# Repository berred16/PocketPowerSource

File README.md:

# PocketPowerSource
Handheld power source for educational purpose

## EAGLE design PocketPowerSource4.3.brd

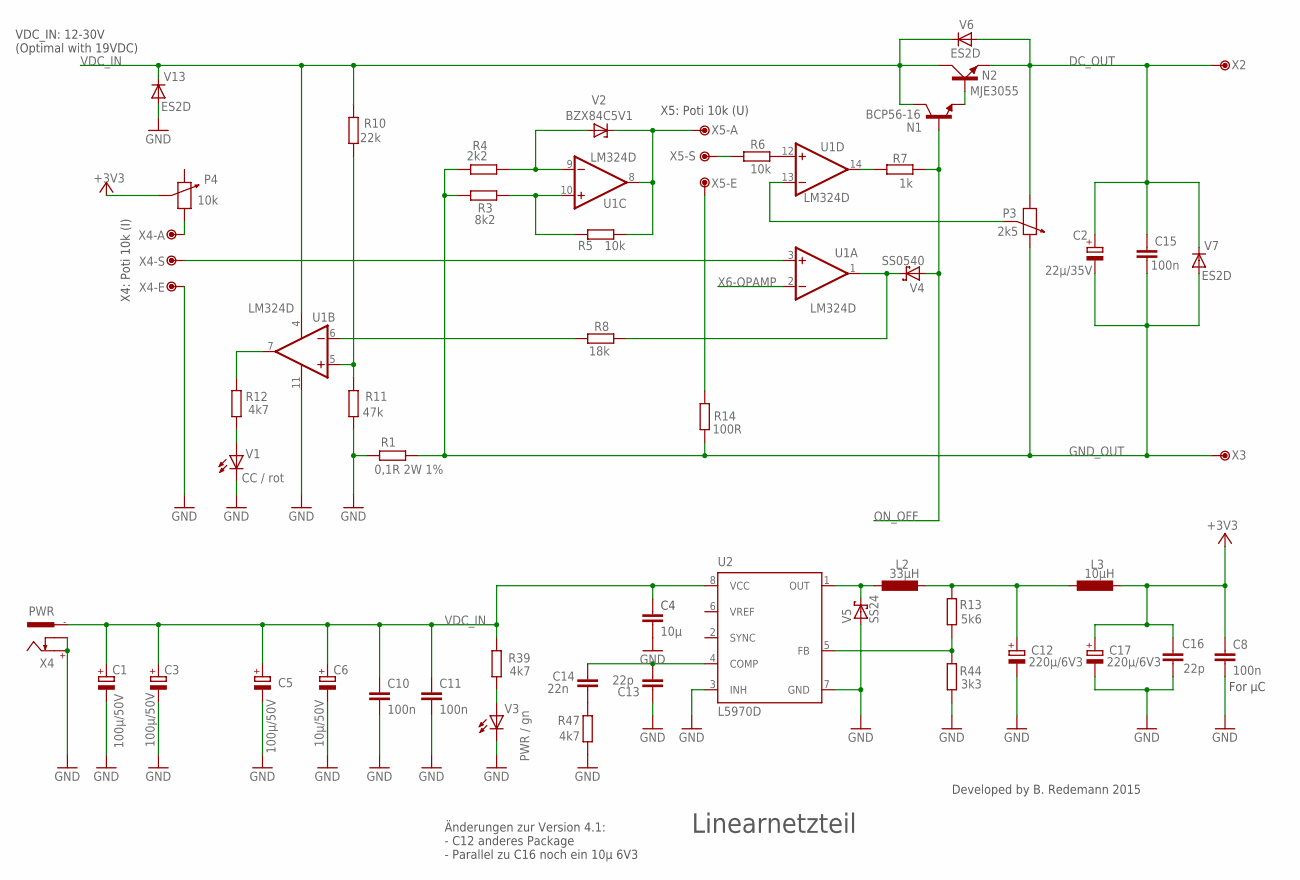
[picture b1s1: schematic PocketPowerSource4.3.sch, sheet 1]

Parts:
C1, C3, C5: 100µ/50V; PANASONIC_F
C2: 22µ/35V; PANASONIC_C
C4: 10µ; C1210
C6: 10µ/50V; PANASONIC_D
C8, C10, C11, C15: 100n; C0603K
C12, C17: 220µ/6V3; PANASONIC_D
C13, C16: 22p; C0805
C14: 22n; C1206
L2: 33µH; POWER-CHOKE_WE-TPC
L3: 10µH; L4540
N1: BCP56-16; PG-SOT-223
N2: MJE3055; TO220AV
P3: 2k5; PT6
P4: 10k; PT6
R1: 0,1R 2W 1%; R2512
R3: 8k2; R0603
R4: 2k2; R0805
R5, R6: 10k; R0603
R7: 1k; R0603
R8: 18k; R1206
R10: 22k; R0603
R11: 47k; R0603
R12, R39, R47: 4k7; R1206
R13: 5k6; R0603
R14: 100R; R0603
R44: 3k3; R0603
U1: LM324D; SO14
U2: L5970D; SO08
V1: CC / rot; LED3MM
V2: BZX84C5V1; TO236
V3: PWR / gn; LED3MM
V4: SS0540; SOD123
V5: SS24; SMB
V6, V7, V13: ES2D; SMB
X2: DC_OUT; P1-13
X3: GND_OUT; P1-13
X4: PWR; 737992-5
X4-A: P_I-A; P1-13
X4-E: P_I-E; P1-13
X4-S: P_I-W; P1-13
X5-A: P_U-A; P1-13
X5-E: P_U-E; P1-13
X5-S: P_U-S; P1-13

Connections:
+3V3: C8.1, C16.2, C17.+, L3.P$2 (2), P4.WIPER (1S); also elsewhere on the board
DC_OUT: C2.+, C15.1, N2.E, P3.RIGHT (1E), V6.A, V7.C, X2.TP; also elsewhere on the board
GND: C1.-, C3.-, C4.2, C5.-, C6.-, C8.2, C10.2, C11.2, C12.-, C13.1, C16.1, C17.-, R1.2, R11.1, R44.1, R47.1, U1.11 (V-), U2.3 (INH), U2.7 (GND), V1.K (C), V3.K (C), V5.A, V13.A, X4.+, X4.K, X4-E.TP; also elsewhere on the board
GND_OUT: C2.-, C15.2, P3.LEFT (1A), R1.1, R3.1, R4.1, R14.2, V7.A, X3.TP; also elsewhere on the board
unnamed: R8.1, U1.6 (-IN)
unnamed: R5.1, U1.8 (OUT), V2.C, X5-A.TP
unnamed: R12.1, U1.7 (OUT)
unnamed: P4.RIGHT (1E), X4-A.TP
unnamed: R12.2, V1.A
unnamed: R8.2, U1.1 (OUT), V4.C
unnamed: R3.2, R5.2, U1.10 (+IN)
unnamed: R4.2, U1.9 (-IN), V2.A
unnamed: N1.3 (E), N2.B
unnamed: R7.2, U1.14 (OUT)
unnamed: C13.2, C14.1, U2.4 (COMP)
unnamed: R10.1, R11.2, U1.5 (+IN)
unnamed: R6.2, U1.12 (+IN)
unnamed: P3.WIPER (1S), U1.13 (-IN)
unnamed: R6.1, X5-S.TP
unnamed: R14.1, X5-E.TP
unnamed: U1.3 (+IN), X4-S.TP
unnamed: C12.+, L2.2, L3.P$1 (1), R13.2
unnamed: R39.1, V3.A
unnamed: R13.1, R44.2, U2.5 (FB)
unnamed: C14.2, R47.2
unnamed: L2.1, U2.1 (OUT), V5.C
ON_OFF: N1.1 (B), R7.1, V4.A; also elsewhere on the board
VDC_IN: C1.+, C3.+, C4.1, C5.+, C6.+, C10.1, C11.1, N1.2 (C), N1.4 (C), N2.C, R10.2, R39.2, U1.4 (V+), U2.8 (VCC), V6.C, V13.C, X4.-1; also elsewhere on the board
X6-OPAMP: U1.2 (-IN); also elsewhere on the board

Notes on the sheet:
Linearnetzteil
VDC_IN: 12-30V (Optimal with 19VDC)
For µC
X4: Poti 10k (I)
X5: Poti 10k (U)
Developed by B. Redemann 2015
Änderungen zur Version 4.1: - C12 anderes Package - Parallel zu C16 noch ein 10µ 6V3

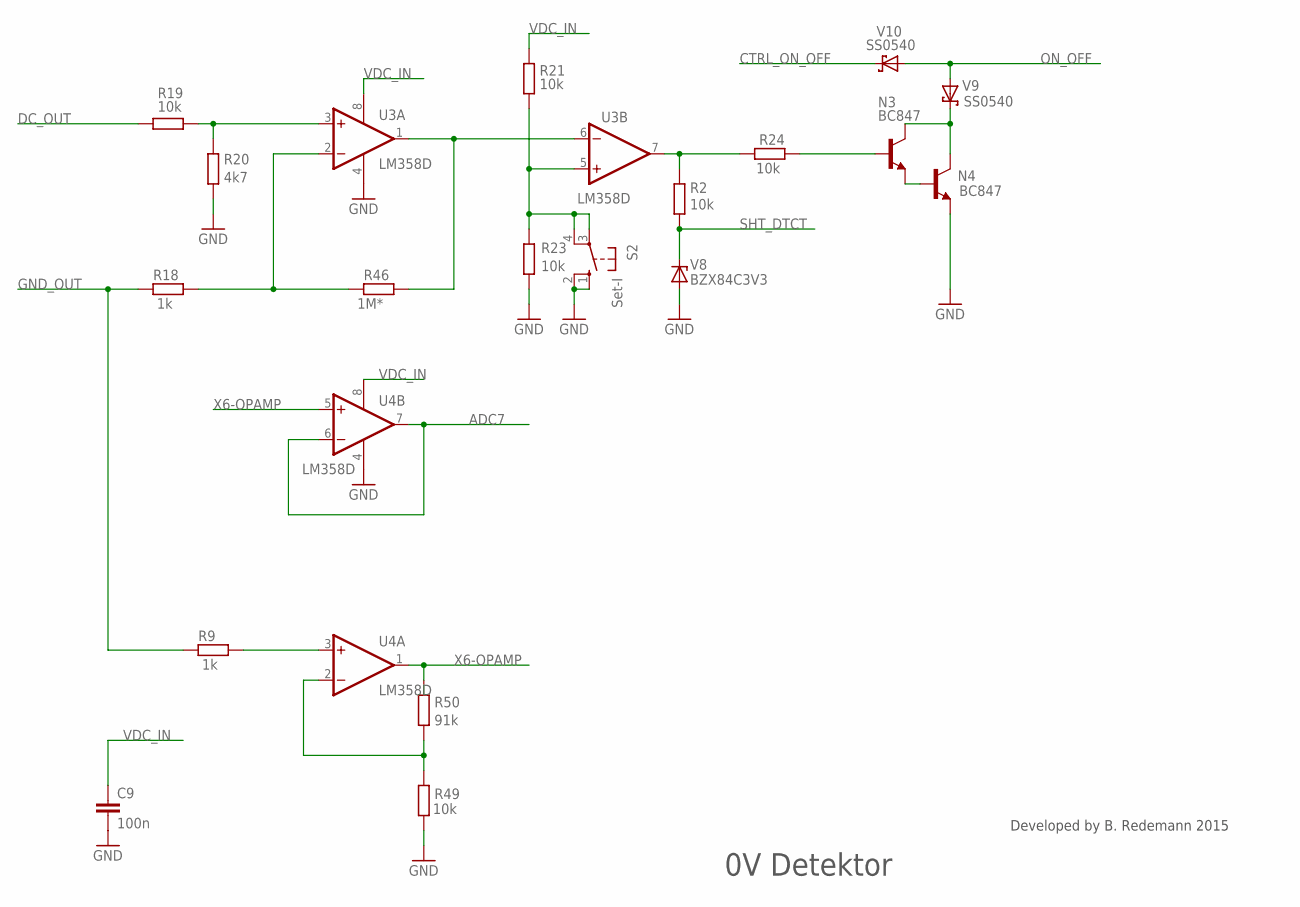
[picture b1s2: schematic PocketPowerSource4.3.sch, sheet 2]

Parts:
C9: 100n; C0603K
N3, N4: BC847; SOT23
R2, R19, R21, R23, R24, R49: 10k; R0603
R9, R18: 1k; R0603
R20: 4k7; R1206
R46: 1M*; R0603
R50: 91k; R0805
S2: Set-I; B3F-10XX
U3, U4: LM358D; SO08
V8: BZX84C3V3; TO236
V9, V10: SS0540; SOD123

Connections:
ADC7: U4.6 (-IN), U4.7 (OUT); also elsewhere on the board
CTRL_ON_OFF: V10.C; also elsewhere on the board
DC_OUT: R19.1; also elsewhere on the board
GND: C9.2, N4.2 (E), R20.1, R23.1, R49.1, S2.1 (S), S2.2 (S1), U3.4 (V-), U4.4 (V-), V8.A; also elsewhere on the board
GND_OUT: R9.1, R18.1; also elsewhere on the board
unnamed: R19.2, R20.2, U3.3 (+IN)
unnamed: R9.2, U4.3 (+IN)
unnamed: N3.1 (B), R24.2
unnamed: R2.2, R24.1, U3.7 (OUT)
unnamed: R18.2, R46.1, U3.2 (-IN)
unnamed: R46.2, U3.1 (OUT), U3.6 (-IN)
unnamed: R21.1, R23.2, S2.3, S2.4 (P1), U3.5 (+IN)
unnamed: R49.2, R50.1, U4.2 (-IN)
unnamed: N3.2 (E), N4.1 (B)
unnamed: N3.3 (C), N4.3 (C), V9.C
ON_OFF: V9.A, V10.A; also elsewhere on the board
SHT_DTCT: R2.1, V8.C; also elsewhere on the board
VDC_IN: C9.1, R21.2, U3.8 (V+), U4.8 (V+); also elsewhere on the board
X6-OPAMP: R50.2, U4.1 (OUT), U4.5 (+IN); also elsewhere on the board

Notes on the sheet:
0V Detektor
Developed by B. Redemann 2015

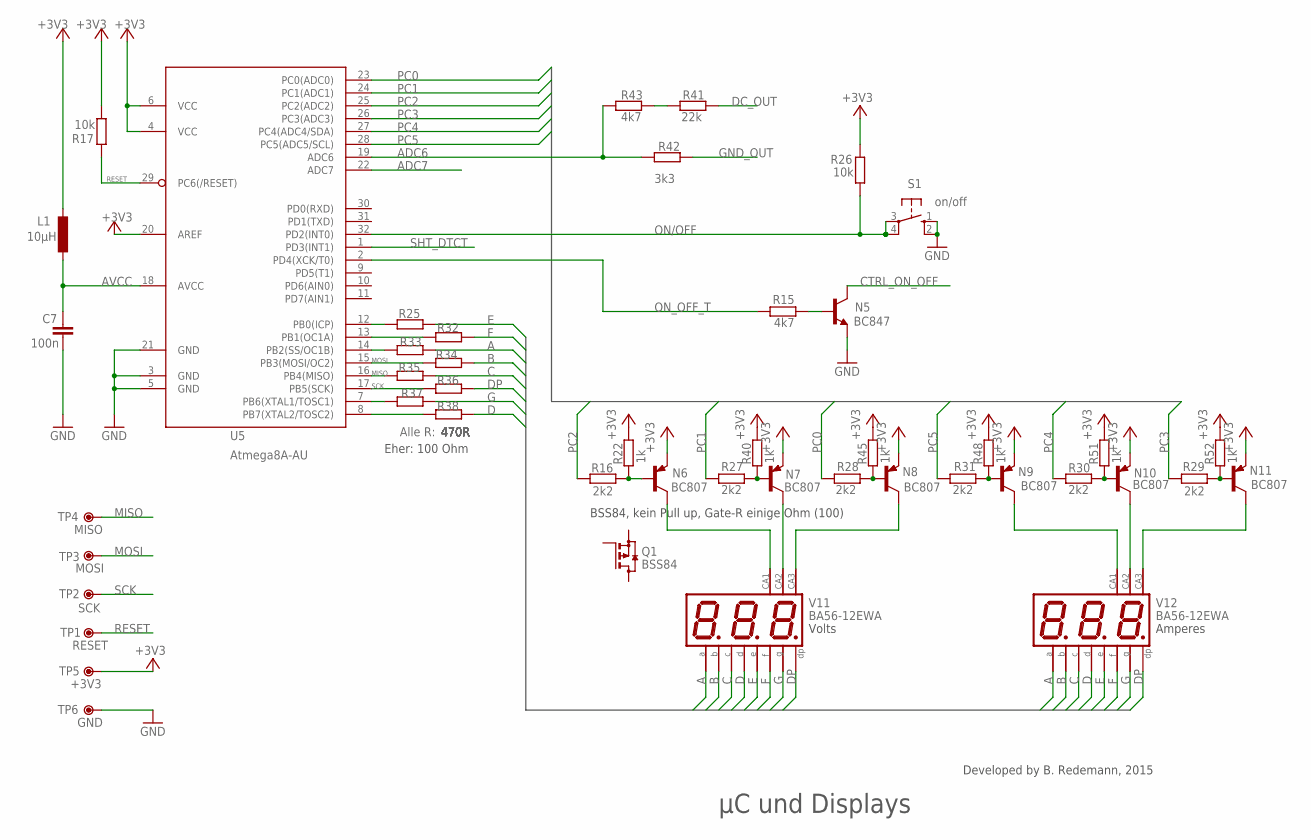
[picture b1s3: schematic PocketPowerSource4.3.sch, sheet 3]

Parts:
C7: 100n; C0603K
L1: 10µH; L2825P
N5: BC847; SOT23
N6, N7, N8, N9, N10, N11: BC807; SOT23-BEC
Q1: BSS84; SOT23
R15, R43: 4k7; R1206
R16, R27, R28, R29, R30, R31: 2k2; R1206
R17, R26: 10k; R0603
R22, R40, R45, R48, R51, R52: 1k; R0603
R25, R32, R33, R34, R35, R36, R37, R38: 470R; R0805
R41: 22k; R0603
R42: 3k3; R0603
S1: on/off; B3F-10XX
TP1: RESET; P1-13
TP2: SCK; P1-13
TP3: MOSI; P1-13
TP4: MISO; P1-13
TP5: +3V3; P1-13
TP6: GND; P1-13
U5: Atmega8A-AU; TQFP32-08
V11, V12: BA56-12EWA; BX56-12

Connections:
+3V3: L1.1, N6.E, N7.E, N8.E, N9.E, N10.E, N11.E, R17.1, R22.2, R26.2, R40.2, R45.2, R48.2, R51.2, R52.2, TP5.TP, U5.4 (VCC), U5.6 (VCC), U5.20 (AREF); also elsewhere on the board
A: R33.1, V11.11 (A), V12.11 (A)
ADC6: R42.1, R43.1, U5.19 (ADC6)
ADC7: U5.22 (ADC7); also elsewhere on the board
AVCC: C7.1, L1.2, U5.18 (AVCC)
B: R34.1, V11.7 (B), V12.7 (B)
C: R35.1, V11.4 (C), V12.4 (C)
CTRL_ON_OFF: N5.3 (C); also elsewhere on the board
D: R38.1, V11.2 (D), V12.2 (D)
DC_OUT: R41.2; also elsewhere on the board
DP: R36.1, V11.3 (DP), V12.3 (DP)
E: R25.1, V11.1 (E), V12.1 (E)
F: R32.1, V11.10 (F), V12.10 (F)
G: R37.1, V11.5 (G), V12.5 (G)
GND: C7.2, N5.2 (E), S1.1 (S), S1.2 (S1), TP6.TP, U5.3 (GND), U5.5 (GND), U5.21 (GND); also elsewhere on the board
GND_OUT: R42.2; also elsewhere on the board
MISO: R35.2, TP4.TP, U5.16 (PB4(MISO))
MOSI: R34.2, TP3.TP, U5.15 (PB3(MOSI/OC2))
unnamed: R41.1, R43.2
unnamed: N5.1 (B), R15.1
unnamed: N6.B, R16.2, R22.1
unnamed: R25.2, U5.12 (PB0(ICP))
unnamed: R32.2, U5.13 (PB1(OC1A))
unnamed: N7.B, R27.2, R40.1
unnamed: N8.B, R28.2, R45.1
unnamed: N10.B, R30.2, R51.1
unnamed: N7.C, V11.9 (CA)
unnamed: N10.C, V12.9 (CA)
unnamed: N8.C, V11.8 (CA)
unnamed: N6.C, V11.12 (CA)
unnamed: N9.C, V12.12 (CA)
unnamed: N11.C, V12.8 (CA)
unnamed: N9.B, R31.2, R48.1
unnamed: N11.B, R29.2, R52.1
unnamed: R33.2, U5.14 (PB2(SS/OC1B))
unnamed: R37.2, U5.7 (PB6(XTAL1/TOSC1))
unnamed: R38.2, U5.8 (PB7(XTAL2/TOSC2))
ON/OFF: R26.1, S1.3, S1.4 (P1), U5.32 (PD2(INT0))
ON_OFF_T: R15.2, U5.2 (PD4(XCK/T0))
PC0: R28.1, U5.23 (PC0(ADC0))
PC1: R27.1, U5.24 (PC1(ADC1))
PC2: R16.1, U5.25 (PC2(ADC2))
PC3: R29.1, U5.26 (PC3(ADC3))
PC4: R30.1, U5.27 (PC4(ADC4/SDA))
PC5: R31.1, U5.28 (PC5(ADC5/SCL))
RESET: R17.2, TP1.TP, U5.29 (PC6(/RESET))
SCK: R36.2, TP2.TP, U5.17 (PB5(SCK))
SHT_DTCT: U5.1 (PD3(INT1)); also elsewhere on the board

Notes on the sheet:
µC und Displays
Alle R:
Volts
Amperes
Developed by B. Redemann, 2015
Eher: 100 Ohm
BSS84, kein Pull up, Gate-R einige Ohm (100)

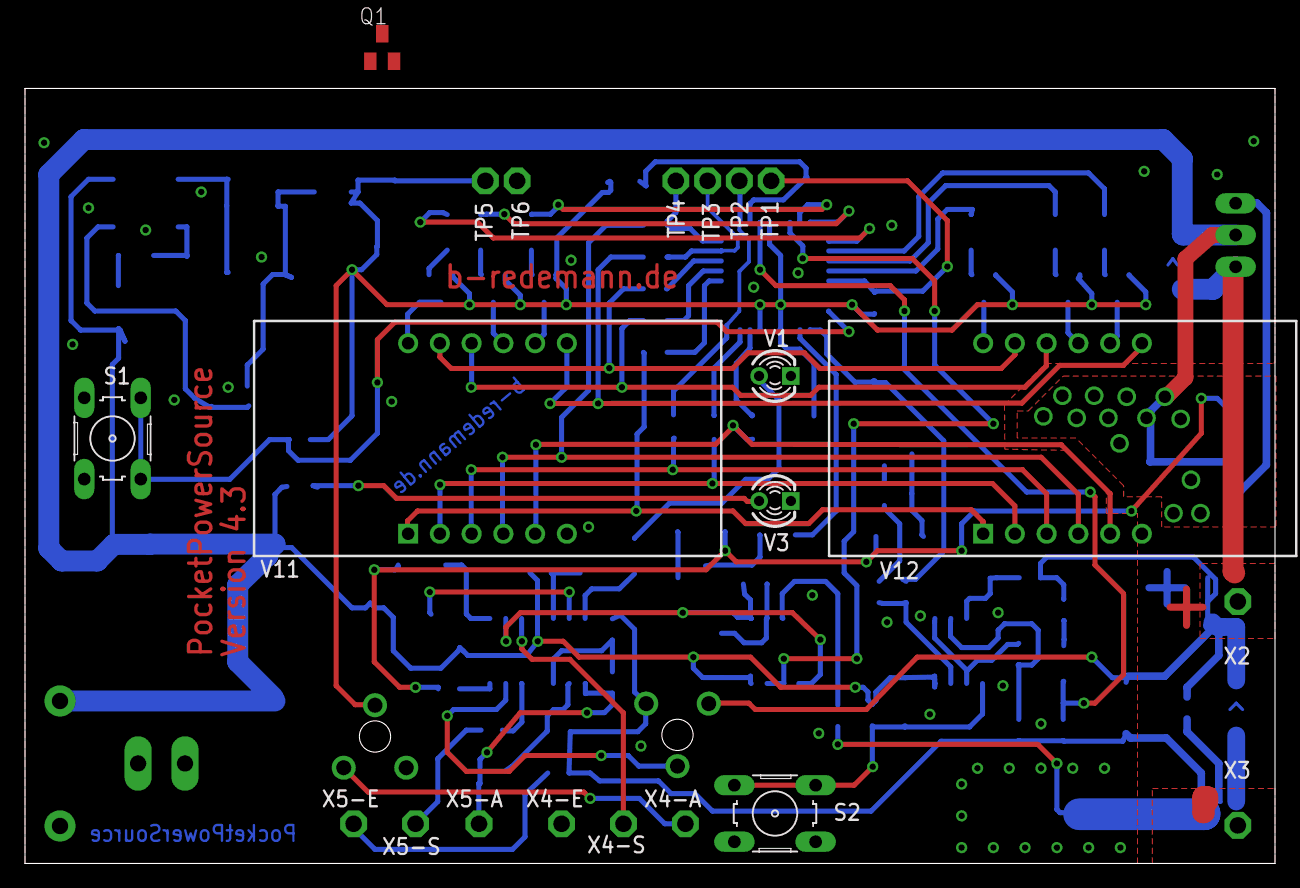
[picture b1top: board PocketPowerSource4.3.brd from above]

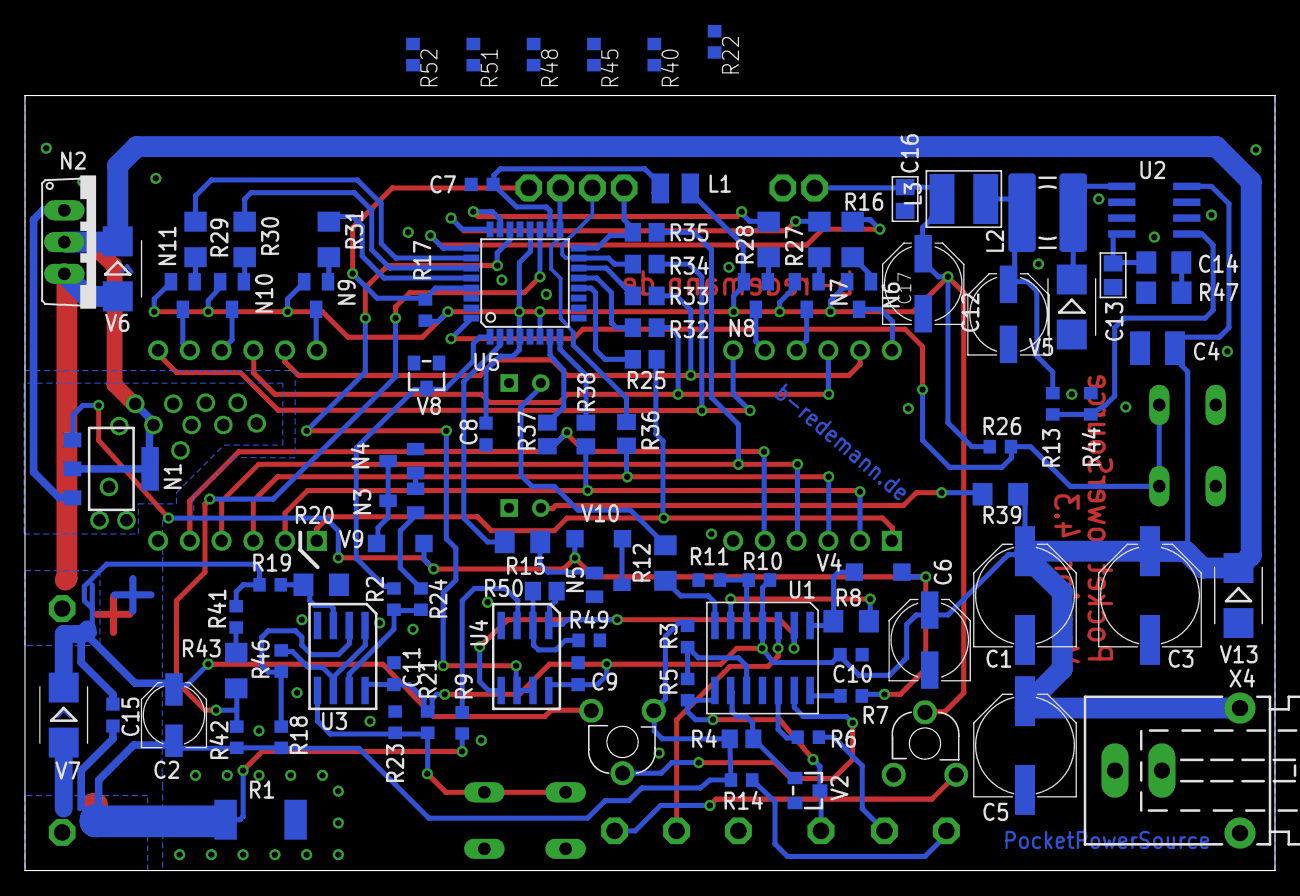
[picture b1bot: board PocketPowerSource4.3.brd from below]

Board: 2 copper layers, 100.0 x 62.0 mm, 121 parts (100 on the bottom side), 83 nets.

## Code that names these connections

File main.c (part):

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
Atmega8/88/162/328 (smd package, 32 pins)

  -> SHT_DETECT PD3 |1------U-----32| PD2 <- Button on/off
  <- Out on/off PD4 |2            31| PD1 free
				GND |3            30| PD0 free
				VCC |4            29| (Reset)
				GND |5            28| PC5 I_AN_tens
				VCC |6            27| PC4 I_AN_ones
			(g)	PB6 |7            26| PC3 I_AN_tenth
    	    (d) PB7 |8            25| PC2 V_AN_tens
           free PD5 |9            24| PC1 V_AN_ones
           free PD6 |10           23| PC0 V_AN_tenth
           free PD7 |11           22| ADC7 (Amperes)
            (e) PB0 |12           21| GND 
            (f) PB1 |13           20| AREF 
            (a) PB2 |14           19| ADC6 (Volts)
		    (b) PB3 |15			  18| AVCC
			(c) PB4 |16-----------17| PB5 (dp)


  ---------------\   />--------------- V (output +, red)
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void toggle(void)
	{
		// toggle to switch on/off the power supply
		// PD2 button, PD4 Out
		sw=PIND & 0x04;  			// read switch at PD2
		sw_os=sw && !sw_last; 		// one shot of switch going on
		sw_last=sw;          		// remember last pass;
		if(sw_os) sw_on = !sw_on; 	// toggle state
		sw_on<<=4;					// left shift because PD4
		PORTD=sw_on;				// output toggle
		sw_on>>=4;					// shift right (back zu origin)
	}

// short detect variables
unsigned char sh;   				// variable for PD3
unsigned char sh_detect;     		// short detect

void short_circuit(void)
	{
		// detect pin PD3 if there is a short circuit
		sh=PIND & 0x08;				// read value at PD3
		sh>>=3;						// right shift PD3 to get 1 or 0
		sh_detect=sh;				// variable for case instruction
		sh<<=3;						// shift left (back zu origin)
	}
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{
switch(sw_on) // display "v1.b off" 
					{
					case 1: // if PD4 = 1
						{
							switch (seg_count)
							{	
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						break;
						}
					
					case 0: // if PD4 = 0, powered on
						{
						switch (sh_detect) // display "short"
							{
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ISR (TIMER2_OVF_vect)
	{
	toggle(); // check the on/off button
	short_circuit(); // check signal at PD3
	display(); // acitvate display
	}

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

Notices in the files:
main.c:
Copyright (C) 2015  Bernhard Redemann (bernd.red@b-redemann.de)
This program is free software: you can redistribute it and/or modify
it under the terms of the GNU General Public License as published by
the Free Software Foundation, either version 3 of the License, or
(at your option) any later version.
